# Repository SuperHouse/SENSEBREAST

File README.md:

SenseBreast Hat for Raspberry Pi
================================
Copyright 2019 SuperHouse Automation Pty Ltd www.superhouse.tv  

Multiple sensors integrated into a Raspberry Pi hat format for use in
construction of a prosthetic breast as part of the Sense Breast project.
Sensor data can be logged locally and accessed via WiFi, or published
to a data broker such as MQTT.

FEATURES
--------

 * BME680 temperature, pressure, humidity, and VOC gas sensor.
 * 9-DOF IMU with I2C interface.
 * Connector for external heart rate sensor.

INSTALLATION
------------
The design is saved as an EAGLE project. EAGLE PCB design software is
available from www.cadsoftusa.com free for non-commercial use. To use
this project download it and place the directory containing these files
into the "eagle" directory on your computer. Then open EAGLE and
navigate to the project.

DISTRIBUTION
------------
The specific terms of distribution of this project are governed by the
license referenced below.

LICENSE
-------
Licensed under the TAPR Open Hardware License (www.tapr.org/OHL).
The "license" folder within this repository also contains a copy of
this license in plain text format.

CREDITS
-------
Software and concept by Kathy Reid
Hardware by Jonathan Oxer <jon@oxer.com.au>

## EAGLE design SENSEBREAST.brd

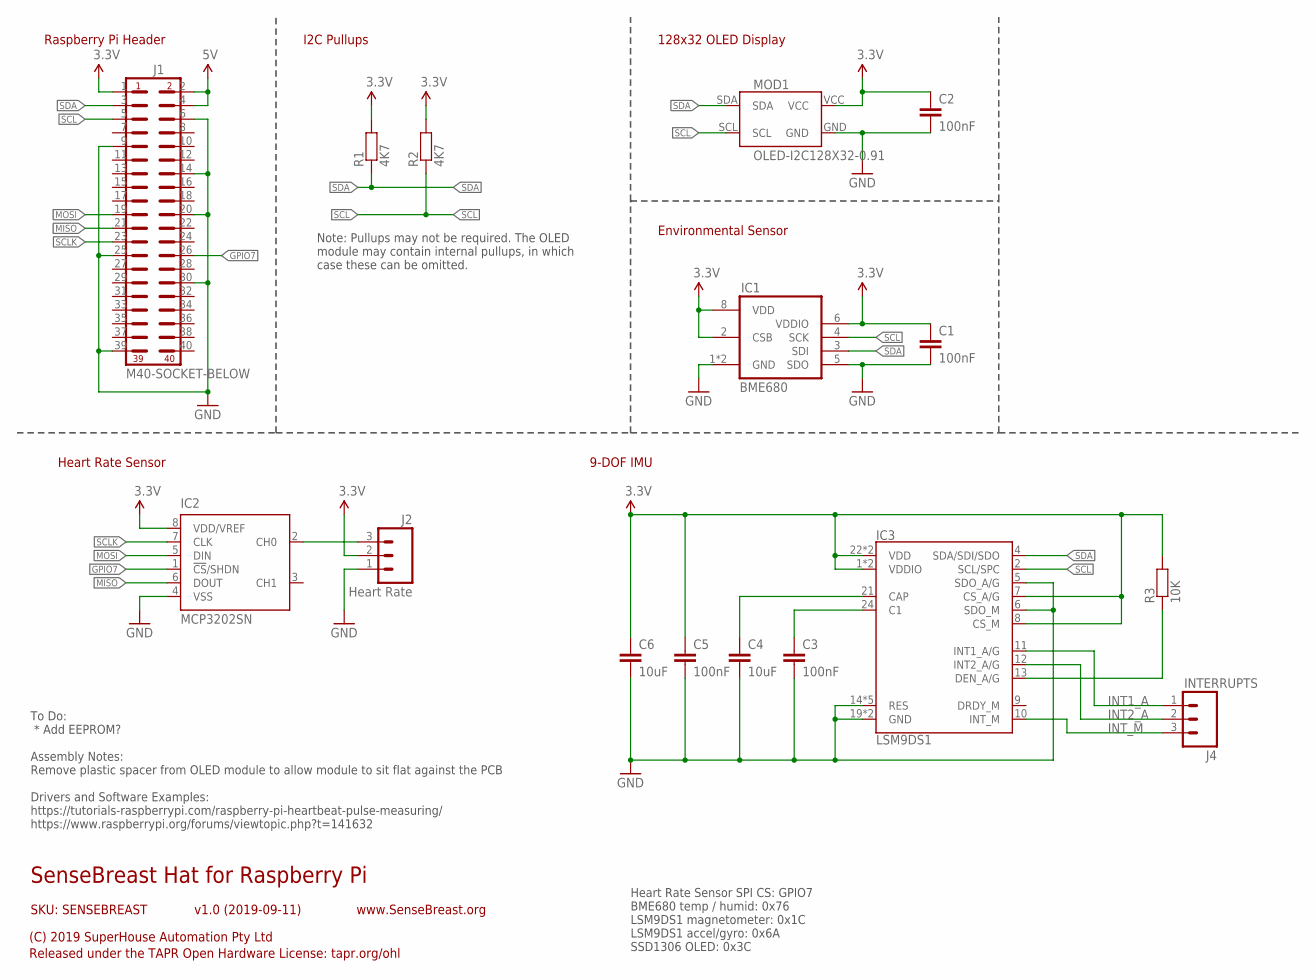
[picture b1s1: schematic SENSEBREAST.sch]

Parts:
C1, C2, C3, C5: 100nF; C0603
C4, C6: 10uF; C0805
IC1: BME680
IC2: MCP3202SN; SO-08
IC3: LSM9DS1; LGA24-8X4
J1: M40-SOCKET-BELOW; 2X20-S-BELOW
J2: Heart Rate; 1X03-S-RA
J4: INTERRUPTS; 1X03
MOD1: OLED-I2C128X32-0.91; OLED-128X32-0.91
R1, R2: 4K7; R0603
R3: 10K; R0603

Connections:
3.3V: C1.1, C2.1, C5.1, C6.1, IC1.2 (CSB), IC1.6 (VDDIO), IC1.8 (VDD), IC2.8 (VDD/VREF), IC3.1 (VDDIO), IC3.3 (VDDIO), IC3.7 (CS_A/G), IC3.8 (CS_M), IC3.22 (VDD), IC3.23 (VDD), J1.1, J2.2, MOD1.VCC, R1.2, R2.2, R3.2
5V: J1.2, J1.4
GND: C1.2, C2.2, C3.2, C4.2, C5.2, C6.2, IC1.1 (GND), IC1.5 (SDO), IC1.7 (GND), IC2.4 (VSS), IC3.5 (SDO_A/G), IC3.6 (SDO_M), IC3.14 (RES), IC3.15 (RES), IC3.16 (RES), IC3.17 (RES), IC3.18 (RES), IC3.19 (GND), IC3.20 (GND), J1.6, J1.9, J1.14, J1.20, J1.25, J1.30, J1.39, J2.1, MOD1.GND
GPIO7: IC2.1 (!CS!/SHDN), J1.26
INT1_A: IC3.11 (INT1_A/G), J4.1
INT2_A: IC3.12 (INT2_A/G), J4.2
INT_M: IC3.10 (INT_M), J4.3
MISO: IC2.6 (DOUT), J1.21
MOSI: IC2.5 (DIN), J1.19
unnamed: IC2.2 (CH0), J2.3
unnamed: IC3.13 (DEN_A/G), R3.1
unnamed: C3.1, IC3.24 (C1)
unnamed: C4.1, IC3.21 (CAP)
SCL: IC1.4 (SCK), IC3.2 (SCL/SPC), J1.5, MOD1.SCL, R2.1
SCLK: IC2.7 (CLK), J1.23
SDA: IC1.3 (SDI), IC3.4 (SDA/SDI/SDO), J1.3, MOD1.SDA, R1.1

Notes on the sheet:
SenseBreast Hat for Raspberry Pi
v1.0 (2019-09-11)
(C) 2019 SuperHouse Automation Pty Ltd
Released under the TAPR Open Hardware License: tapr.org/ohl
www.SenseBreast.org
SKU: SENSEBREAST
Raspberry Pi Header
128x32 OLED Display
Environmental Sensor
I2C Pullups
Note: Pullups may not be required. The OLED module may contain internal pullups, in which case these can be omitted.
To Do: * Add EEPROM? Assembly Notes: Remove plastic spacer from OLED module to allow module to sit flat against the PCB Drivers and Software Examples: https://tutorials-raspberrypi.com/raspberry-pi-heartbeat-pulse-measuring/ https://www.raspberrypi.org/forums/viewtopic.php?t=141632
Heart Rate Sensor
9-DOF IMU
Heart Rate Sensor SPI CS: GPIO7 BME680 temp / humid: 0x76 LSM9DS1 magnetometer: 0x1C LSM9DS1 accel/gyro: 0x6A SSD1306 OLED: 0x3C

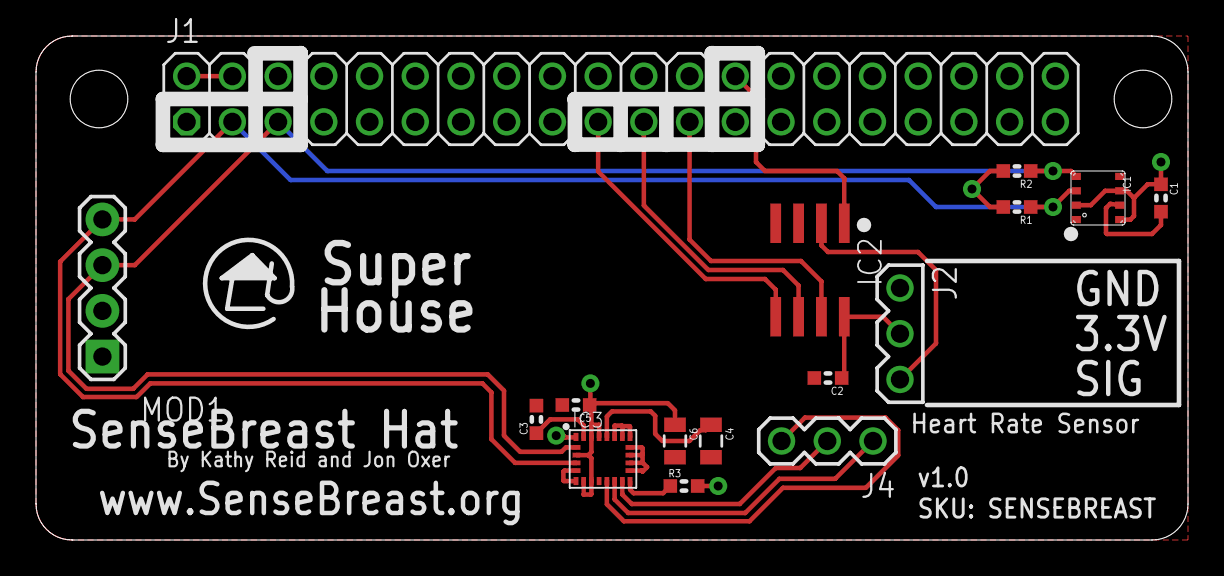
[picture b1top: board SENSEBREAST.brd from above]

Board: 2 copper layers, 64.0 x 28.0 mm, 16 parts (0 on the bottom side), 16 nets.

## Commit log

2019-09-10 Initial project import
2019-09-12 Replaced BME280 with BME680 to allow detection of VOC levels in the environment
2019-09-13 Final routing, plus ERC and DRC for v1.0 release
